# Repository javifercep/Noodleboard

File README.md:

# Noodleboard
Arduino form factor board with USB 2.0 High speed based on STM32F405 MCU.
It has been developed for the [MuBA project](https://gitlab.euridies.com/javi/MuBA)

## Features
 * STM32F405RGT6 microcontroller featuring 32-bit ARM Cortex-M4F core, 1 MB Flash, 192 KB RAM in an LQFP64 package
 * Extension header fully compatible with Arduino™ form-factor
 * USB3300: USB OTG HS with micro-AB connector
 * Board power supply: through USB bus.
 * External application power supply: 3.3 V and 5 V
 * Four green user LEDs
 * Reset button
 * Headers for programming and debugging through SWD protocol

## [Pin map](pin-map)

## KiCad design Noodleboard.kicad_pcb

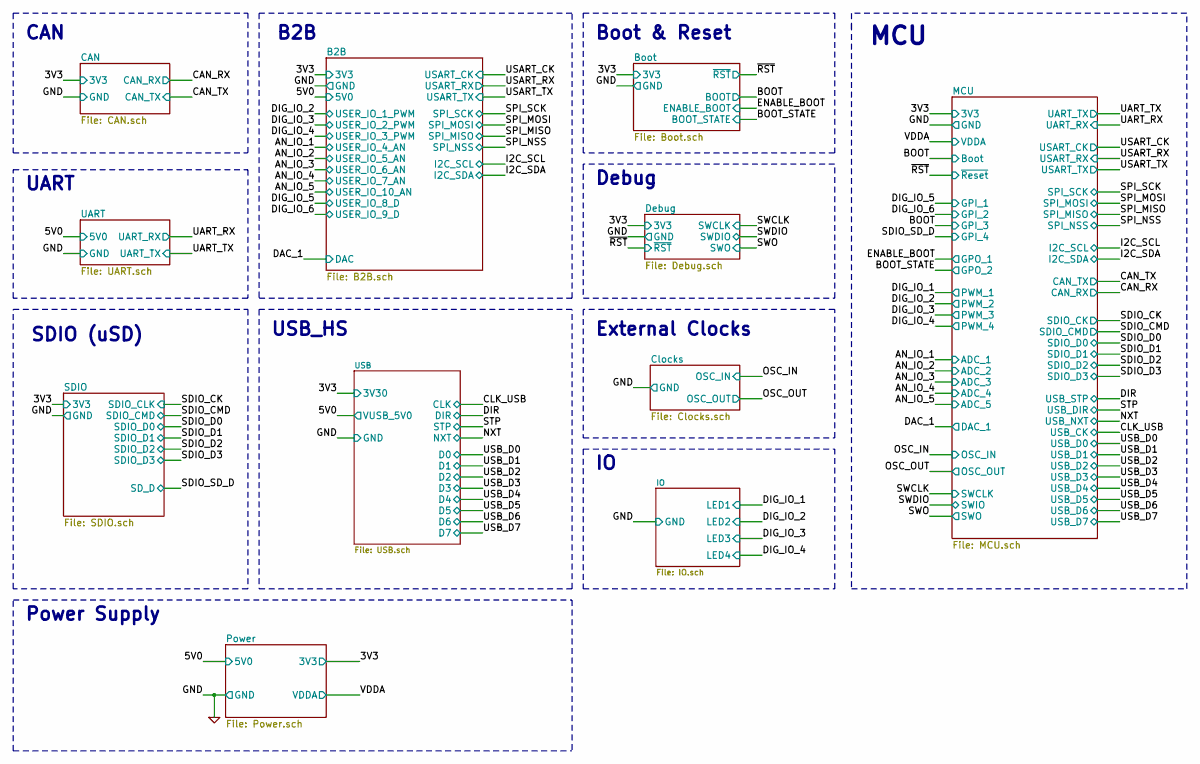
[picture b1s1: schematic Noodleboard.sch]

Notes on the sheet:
Power Supply
USB_HS
Debug
External Clocks
MCU
Boot & Reset
CAN
UART
B2B
SDIO (uSD)

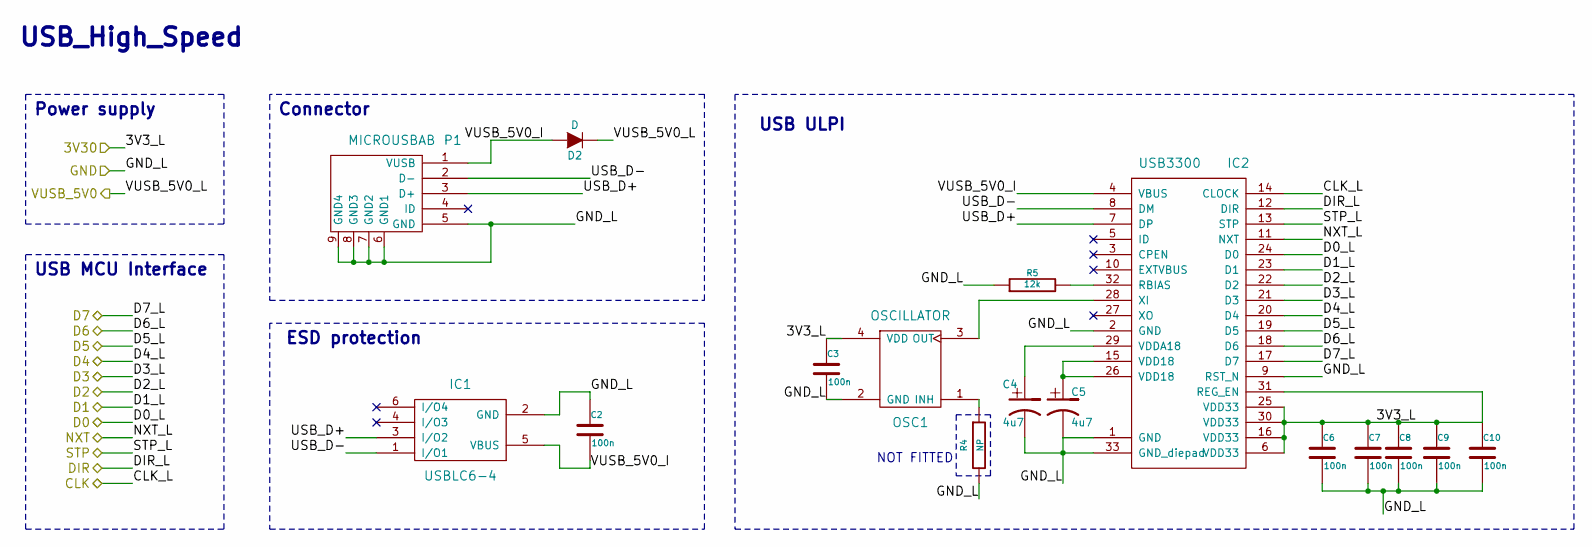
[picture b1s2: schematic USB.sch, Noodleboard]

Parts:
C2, C3, C6, C7, C8, C9, C10: 100n; C_0603_HandSoldering
C4, C5: 4u7; C_0805_HandSoldering
D2: D; SMA_Handsoldering
IC1: USBLC6-4; SOT-23-6
IC2: USB3300; QFN-32-1EP_5x5mm_Pitch0.5mm
OSC1: OSCILLATOR; 26MHZOSC
P1: MICROUSBAB; uUSB-AB
R4: NP; R_0603_HandSoldering
R5: 12k; R_0603_HandSoldering; Tolerancia 1%

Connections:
/B2B/3V3: C3.1, C6.1, C7.1, C8.1, C9.1, C10.1, IC2.6 (VDD33), IC2.16 (VDD33), IC2.25 (VDD33), IC2.30 (VDD33), IC2.31 (REG_EN), OSC1.4 (VDD); also elsewhere on the board
/B2B/5V0: D2.1 (K); also elsewhere on the board
/USB/CLK: IC2.14 (CLOCK); also elsewhere on the board
/USB/D0: IC2.24 (D0); also elsewhere on the board
/USB/D1: IC2.23 (D1); also elsewhere on the board
/USB/D2: IC2.22 (D2); also elsewhere on the board
/USB/D3: IC2.21 (D3); also elsewhere on the board
/USB/D4: IC2.20 (D4); also elsewhere on the board
/USB/D5: IC2.19 (D5); also elsewhere on the board
/USB/D6: IC2.18 (D6); also elsewhere on the board
/USB/D7: IC2.17 (D7); also elsewhere on the board
/USB/DIR: IC2.12 (DIR); also elsewhere on the board
/USB/NXT: IC2.11 (NXT); also elsewhere on the board
/USB/STP: IC2.13 (STP); also elsewhere on the board
/USB/USB_D+: IC1.3 (I/O2), IC2.7 (DP), P1.3 (D+)
/USB/USB_D-: IC1.1 (I/O1), IC2.8 (DM), P1.2 (D-)
/USB/VUSB_5V0_I: C2.2, D2.2 (A), IC1.5 (VBUS), IC2.4 (VBUS), P1.1 (VUSB)
GND: C2.1, C3.2, C4.2, C5.2, C6.2, C7.2, C8.2, C9.2, C10.2, IC1.2 (GND), IC2.1 (GND), IC2.2 (GND), IC2.9 (RST_N), IC2.33 (GND_diepad), OSC1.2 (GND), P1.5 (GND), P1.6 (GND1), P1.7 (GND2), P1.8 (GND3), P1.9 (GND4), R4.2, R5.1; also elsewhere on the board
unnamed: C4.1, IC2.29 (VDDA18)
unnamed: C5.1, IC2.15 (VDD18), IC2.26 (VDD18)
unnamed: IC2.28 (XI), OSC1.3 (OUT)
unnamed: IC2.32 (RBIAS), R5.2
unnamed: OSC1.1 (INH), R4.1

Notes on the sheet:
Power supply
USB_High_Speed
NOT FITTED
Connector
ESD protection
USB MCU Interface
USB ULPI

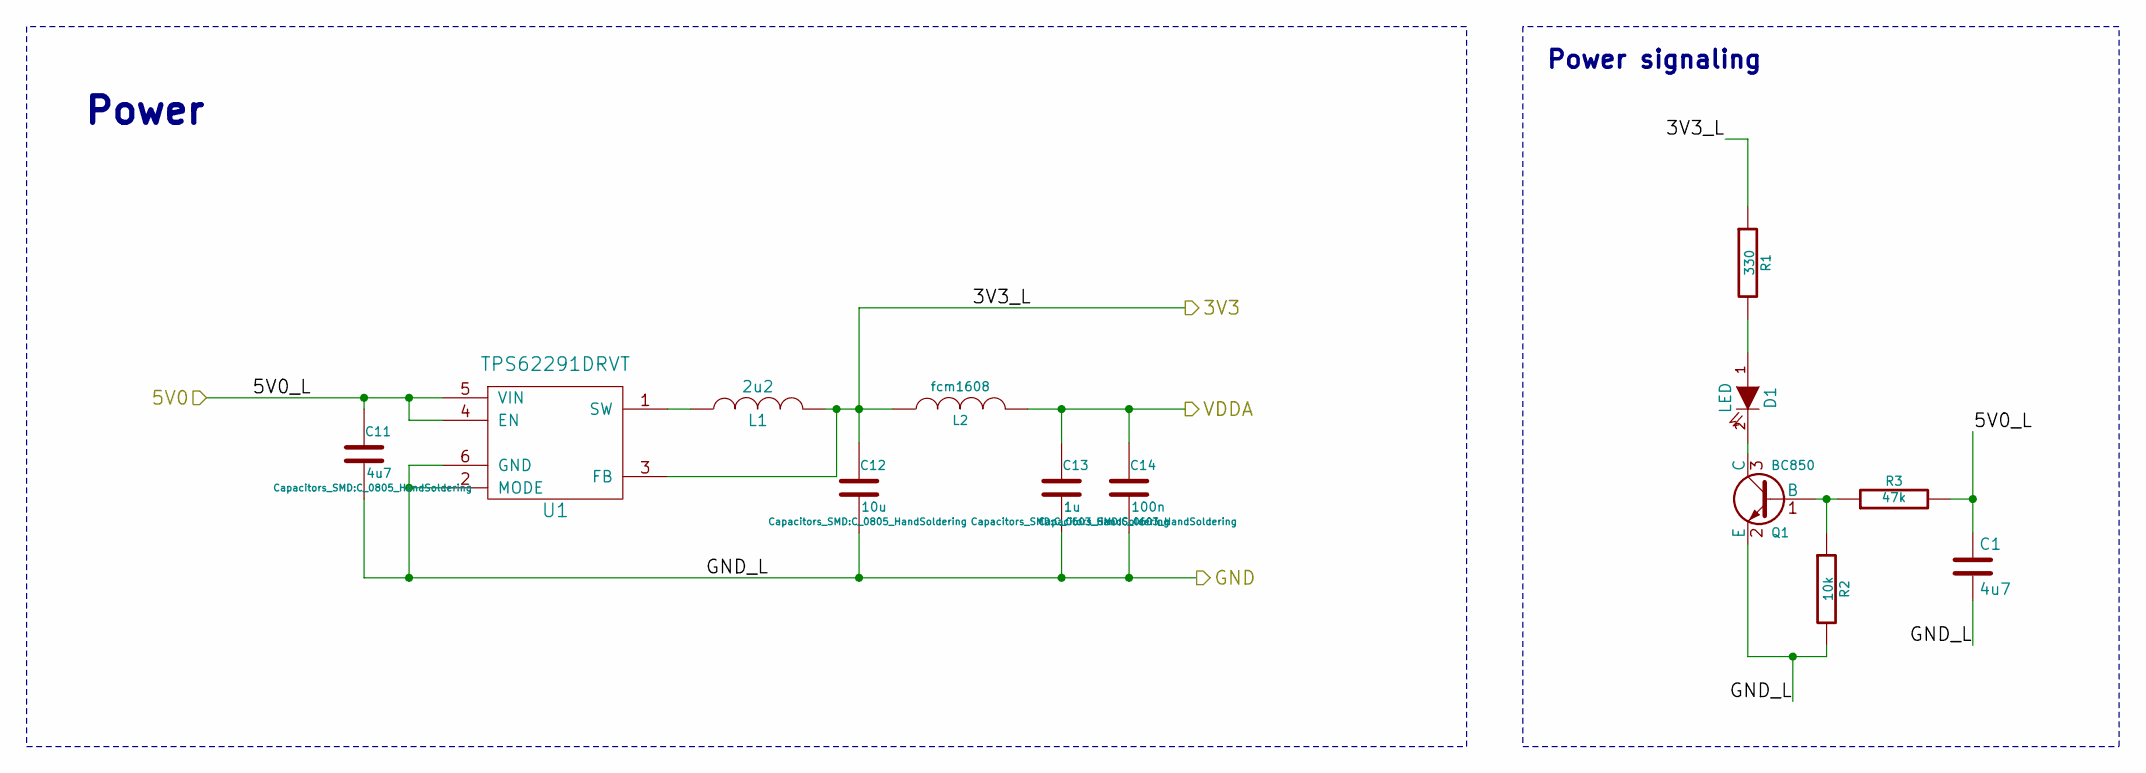
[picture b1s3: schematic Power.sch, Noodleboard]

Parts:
C1: 4u7; C_0805_HandSoldering
C11: 4u7; C_0805_HandSoldering; Part Number GRM188R60J475KE19D
C12: 10u; C_0805_HandSoldering; Part Number C1608X5R0J106M
C13: 1u; C_0603_HandSoldering
C14: 100n; C_0603_HandSoldering
D1: LED; LED-0805
L1: 2u2; SMD_1008; Part Number 74479887222A
L2: fcm1608; R_0603_HandSoldering
Q1: BC850; SOT-23_Handsoldering
R1: 330; R_0603_HandSoldering
R2: 10k; R_0603_HandSoldering
R3: 47k; R_0603_HandSoldering
U1: TPS62291DRVT; S-PWSON-N6

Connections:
/B2B/3V3: C12.1, L1.2, L2.1, R1.1, U1.3 (FB); also elsewhere on the board
/B2B/5V0: C1.1, C11.1, R3.2, U1.4 (EN), U1.5 (VIN); also elsewhere on the board
/MCU/VDDA: C13.1, C14.1, L2.2; also elsewhere on the board
GND: C1.2, C11.2, C12.2, C13.2, C14.2, Q1.2 (E), R2.2, U1.2 (MODE), U1.6 (GND); also elsewhere on the board
unnamed: D1.1 (A), R1.2
unnamed: D1.2 (K), Q1.3 (C)
unnamed: L1.1, U1.1 (SW)
unnamed: Q1.1 (B), R2.1, R3.1

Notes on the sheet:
Power
Power signaling

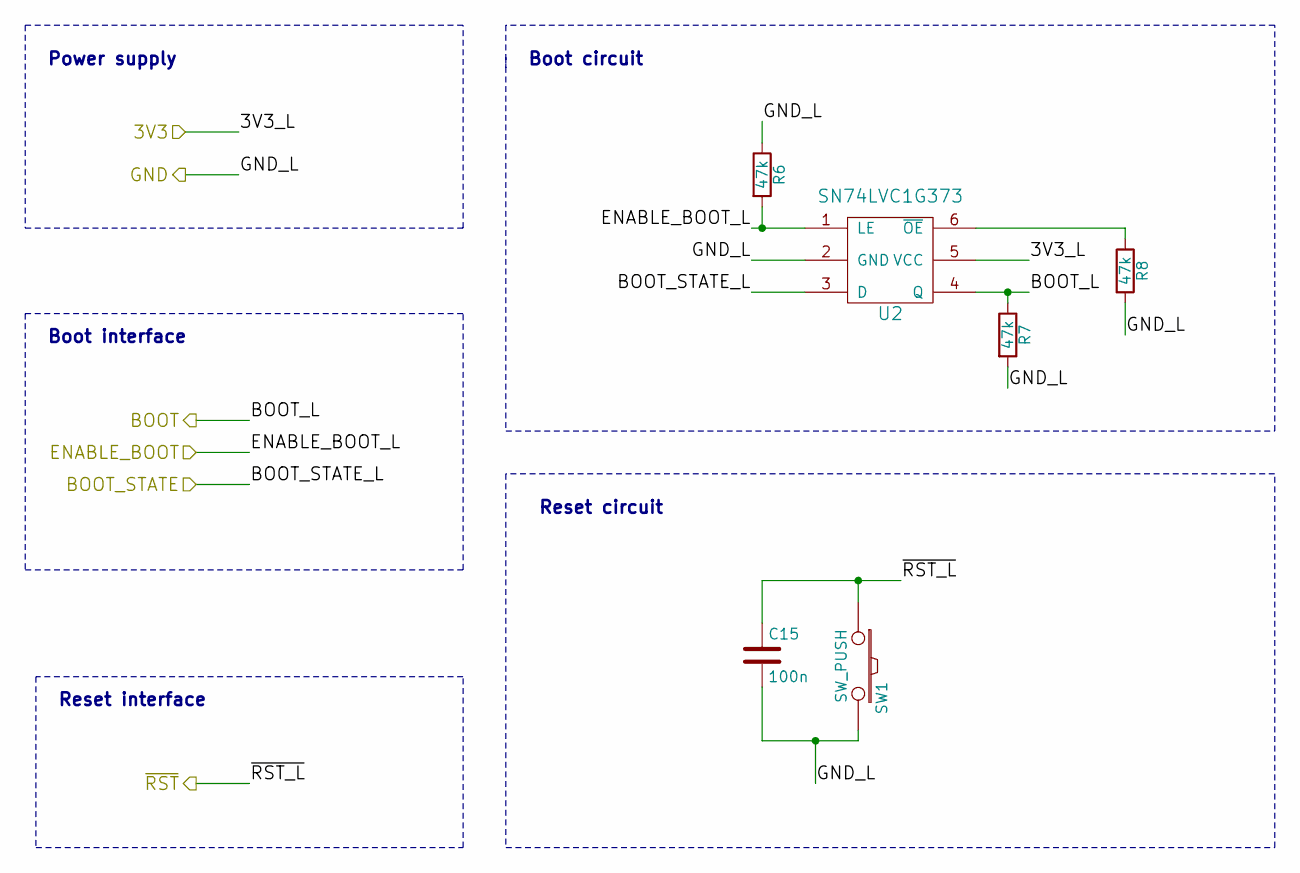
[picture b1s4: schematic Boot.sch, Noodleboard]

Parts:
C15: 100n; C_0603_HandSoldering
R6, R7, R8: 47k; R_0603_HandSoldering
SW1: SW_PUSH; SW_PUSH_SMALL_SMD
U2: SN74LVC1G373; SOT-23-6

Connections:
/B2B/3V3: U2.5 (VCC); also elsewhere on the board
/Boot/BOOT: R7.1, U2.4 (Q); also elsewhere on the board
/Boot/BOOT_STATE: U2.3 (D); also elsewhere on the board
/Boot/ENABLE_BOOT: R6.2, U2.1 (LE); also elsewhere on the board
/Boot/~RST: C15.1, SW1.1; also elsewhere on the board
GND: C15.2, R6.1, R7.2, R8.2, SW1.2, U2.2 (GND); also elsewhere on the board
unnamed: R8.1, U2.6 (~OE)

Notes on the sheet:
Reset circuit
Boot circuit
Power supply
Boot interface
Reset interface

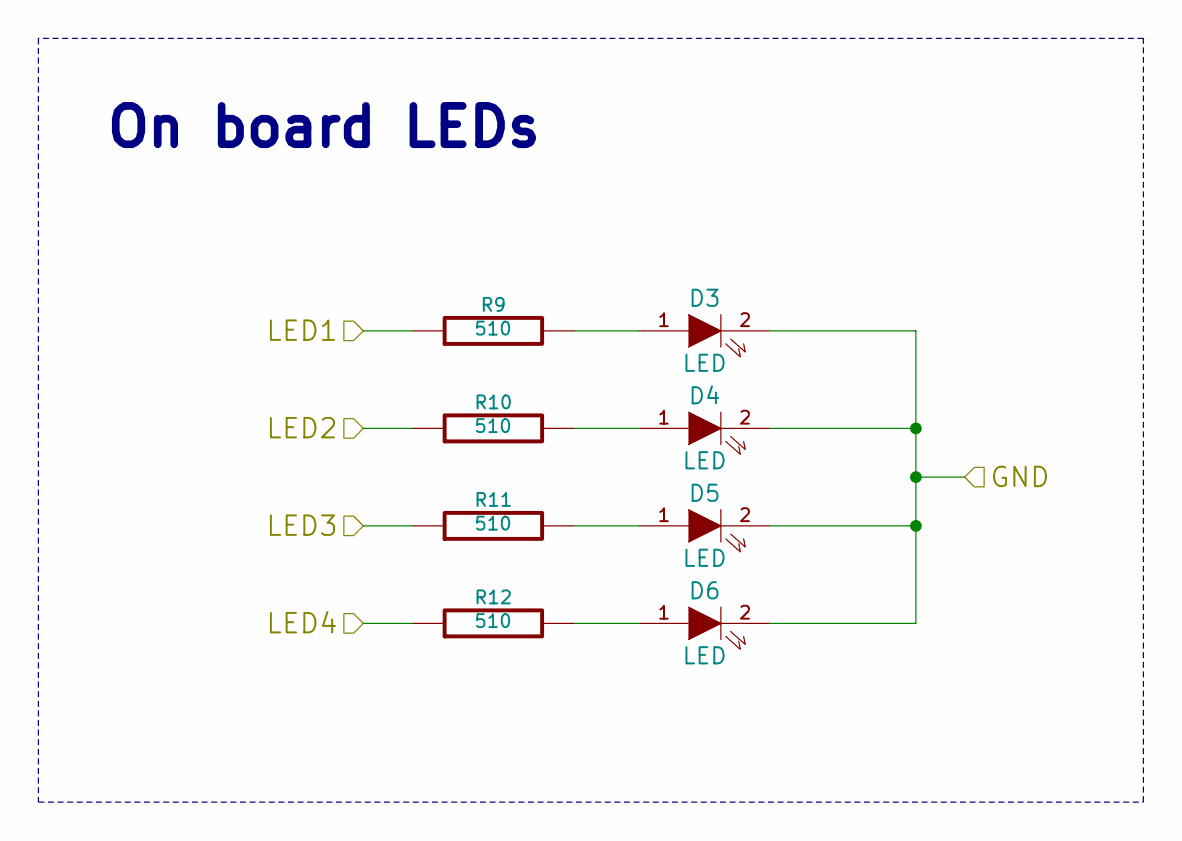
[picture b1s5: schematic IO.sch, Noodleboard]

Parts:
D3, D4, D5, D6: LED; LED-0805
R9, R10, R11, R12: 510; R_0603_HandSoldering

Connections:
/IO/LED1: R9.1; also elsewhere on the board
/IO/LED2: R10.1; also elsewhere on the board
/IO/LED3: R11.1; also elsewhere on the board
/IO/LED4: R12.1; also elsewhere on the board
GND: D3.2 (K), D4.2 (K), D5.2 (K), D6.2 (K); also elsewhere on the board
unnamed: D3.1 (A), R9.2
unnamed: D4.1 (A), R10.2
unnamed: D5.1 (A), R11.2
unnamed: D6.1 (A), R12.2

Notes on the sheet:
On board LEDs

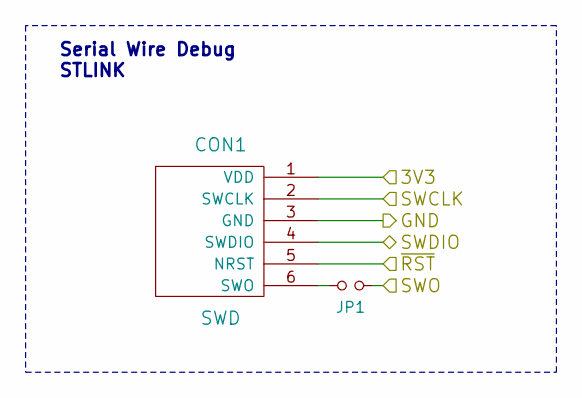
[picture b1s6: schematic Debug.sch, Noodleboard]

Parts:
CON1: SWD; Pin_Header_Straight_1x06
JP1: Jumper_NO_Small; R_0603_HandSoldering

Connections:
/B2B/3V3: CON1.1 (VDD); also elsewhere on the board
/B2B/SPI_SCK: JP1.2; also elsewhere on the board
/Boot/~RST: CON1.5 (NRST); also elsewhere on the board
/Debug/SWCLK: CON1.2 (SWCLK); also elsewhere on the board
/Debug/SWDIO: CON1.4 (SWDIO); also elsewhere on the board
GND: CON1.3 (GND); also elsewhere on the board
unnamed: CON1.6 (SWO), JP1.1

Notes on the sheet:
Serial Wire Debug STLINK

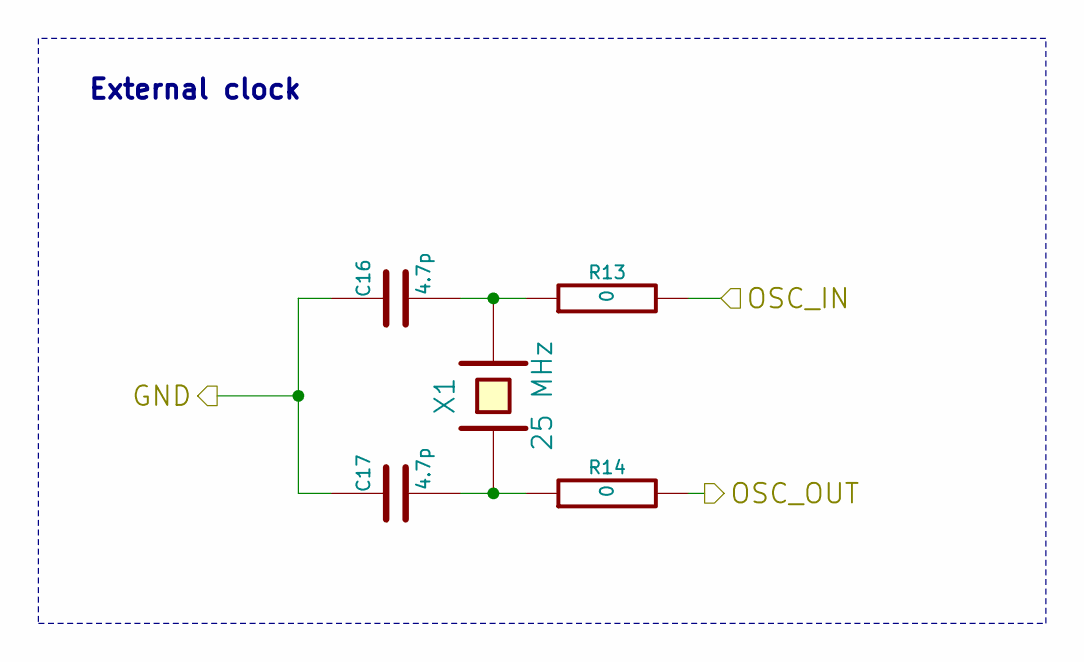
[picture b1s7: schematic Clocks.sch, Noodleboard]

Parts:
C16, C17: 4.7p; C_0603_HandSoldering
R13, R14: 0; R_0603_HandSoldering
X1: 25 MHz; 7A-25.000MAAJ-T

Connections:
/Clocks/OSC_IN: R13.2; also elsewhere on the board
/Clocks/OSC_OUT: R14.2; also elsewhere on the board
GND: C16.1, C17.1; also elsewhere on the board
unnamed: C16.2, R13.1, X1.2
unnamed: C17.2, R14.1, X1.1

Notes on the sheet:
External clock

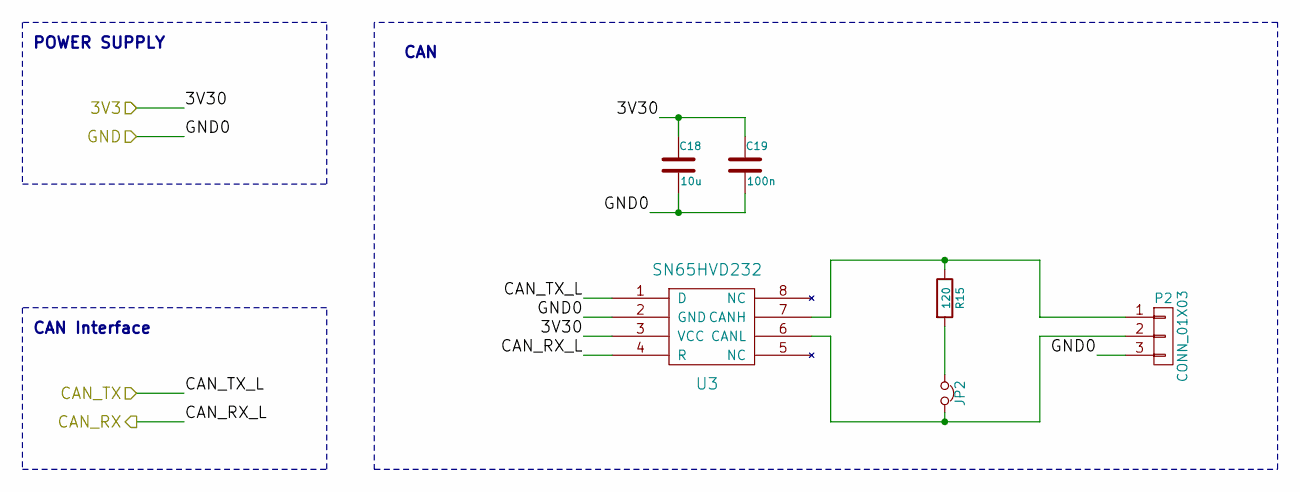
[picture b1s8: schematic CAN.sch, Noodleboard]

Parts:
C18: 10u; C_0805_HandSoldering
C19: 100n; C_0603_HandSoldering
JP2: Jumper_NC_Small; AYZ-SlideSwitches
P2: CONN_01X03; Pin_Header_Straight_1x03
R15: 120; R_0805_HandSoldering
U3: SN65HVD232; SOIC-8_3.9x4.9mm_Pitch1.27mm

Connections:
/B2B/3V3: C18.1, C19.1, U3.3 (VCC); also elsewhere on the board
/CAN/CAN_RX: U3.4 (R); also elsewhere on the board
/CAN/CAN_TX: U3.1 (D); also elsewhere on the board
GND: C18.2, C19.2, P2.3, U3.2 (GND); also elsewhere on the board
unnamed: JP2.1, R15.2
unnamed: JP2.2, P2.2, U3.6 (CANL)
unnamed: P2.1, R15.1, U3.7 (CANH)

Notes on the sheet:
POWER SUPPLY
CAN
CAN Interface

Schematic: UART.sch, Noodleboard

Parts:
C20, C21, C22, C23, C24: 1u; C_0603_HandSoldering
P3: CONN_01X03; Pin_Header_Straight_1x03
U4: MAX232; SOIC-16_3.9x9.9mm_Pitch1.27mm

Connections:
/B2B/5V0: C24.1, U4.16 (VCC); also elsewhere on the board
/MCU/UART_RX: U4.12 (R1OUT); also elsewhere on the board
/MCU/UART_TX: U4.11 (T1IN); also elsewhere on the board
GND: C22.1, C23.1, C24.2, P3.1, U4.15 (GND); also elsewhere on the board
unnamed: C20.1, U4.1 (C1+)
unnamed: C20.2, U4.3 (C1-)
unnamed: C21.1, U4.4 (C2+)
unnamed: C21.2, U4.5 (C2-)
unnamed: C22.2, U4.2 (V+)
unnamed: C23.2, U4.6 (V-)
unnamed: P3.2, U4.14 (T1OUT)
unnamed: P3.3, U4.13 (R1IN)

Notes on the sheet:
POWER SUPPLY
UART

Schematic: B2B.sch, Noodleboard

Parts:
P4: CONN_01X14; Pin_Header_Straight_1x14
P5: CONN_02X07; Pin_Header_Straight_2x07

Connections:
/B2B/3V3: P4.1, P5.1; also elsewhere on the board
/B2B/5V0: P4.13, P5.12; also elsewhere on the board
/B2B/DAC: P4.14; also elsewhere on the board
/B2B/I2C_SCL: P4.11; also elsewhere on the board
/B2B/I2C_SDA: P4.12; also elsewhere on the board
/B2B/SPI_MISO: P4.8; also elsewhere on the board
/B2B/SPI_MOSI: P4.7; also elsewhere on the board
/B2B/SPI_NSS: P4.9; also elsewhere on the board
/B2B/SPI_SCK: P4.6; also elsewhere on the board
/B2B/USART_CK: P4.2; also elsewhere on the board
/B2B/USART_RX: P4.3; also elsewhere on the board
/B2B/USART_TX: P4.4; also elsewhere on the board
/IO/LED2: P5.3; also elsewhere on the board
/IO/LED3: P5.5; also elsewhere on the board
/IO/LED4: P5.7; also elsewhere on the board
/MCU/ADC_1: P5.11; also elsewhere on the board
/MCU/ADC_2: P5.13; also elsewhere on the board
/MCU/ADC_3: P5.2; also elsewhere on the board
/MCU/ADC_4: P5.4; also elsewhere on the board
/MCU/ADC_5: P5.14; also elsewhere on the board
/MCU/GPI_1: P5.8; also elsewhere on the board
/MCU/GPI_2: P5.10; also elsewhere on the board
GND: P4.5, P4.10, P5.6, P5.9; also elsewhere on the board

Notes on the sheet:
Board to board connector

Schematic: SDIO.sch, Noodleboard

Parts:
R16, R17, R18, R19, R20: 47K; R_0603_HandSoldering
R21: 0; R_0603_HandSoldering
U5: SD_CARD; uSDCard

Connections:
/B2B/3V3: R16.2, R17.2, R18.2, R19.2, R20.2, U5.4 (VDD); also elsewhere on the board
/MCU/GPI_4: R21.2; also elsewhere on the board
/MCU/SDIO_CK: U5.5 (CLK); also elsewhere on the board
/MCU/SDIO_CMD: R16.1, U5.3 (CMD); also elsewhere on the board
/MCU/SDIO_D0: R17.1, U5.7 (DAT0); also elsewhere on the board
/MCU/SDIO_D1: R18.1, U5.8 (DAT1); also elsewhere on the board
/MCU/SDIO_D2: R19.1, U5.1 (DAT2); also elsewhere on the board
/MCU/SDIO_D3: R20.1, U5.2 (CD/DAT3); also elsewhere on the board
/SDIO/CD: R21.1, U5.10 (CD)
GND: U5.6 (VSS), U5.9 (DL(GND)); also elsewhere on the board

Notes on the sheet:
SD Card Connector
Power supply
SDIO interface
SD Card detection

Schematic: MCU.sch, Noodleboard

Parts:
C25, C26: 2u2; C_0805_HandSoldering
C27, C28, C29, C30, C32: 100n; C_0603_HandSoldering
C31: 1u; C_0603_HandSoldering
C33: 4u7; C_0805_HandSoldering
JP3, JP4: Jumper_NO_Small; R_0603_HandSoldering
R22: 0; R_0603_HandSoldering
R23: 1K; R_0603_HandSoldering
R24: 47; R_0603_HandSoldering
U6: STM32F405RGT6; LQFP-64_10x10mm_Pitch0.5mm

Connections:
/B2B/3V3: C27.2, C28.1, C29.2, C30.2, C32.2, C33.1, R24.1, U6.19 (VDD), U6.32 (VDD), U6.48 (VDD), U6.64 (VDD); also elsewhere on the board
/B2B/DAC: U6.20 (PA4); also elsewhere on the board
/B2B/I2C_SCL: U6.61 (PB8); also elsewhere on the board
/B2B/I2C_SDA: U6.62 (PB9); also elsewhere on the board
/B2B/SPI_MISO: U6.56 (PB4); also elsewhere on the board
/B2B/SPI_MOSI: U6.23 (PA7); also elsewhere on the board
/B2B/SPI_NSS: U6.50 (PA15); also elsewhere on the board
/B2B/SPI_SCK: U6.55 (PB3); also elsewhere on the board
/B2B/USART_CK: U6.41 (PA8); also elsewhere on the board
/B2B/USART_RX: U6.43 (PA10); also elsewhere on the board
/B2B/USART_TX: U6.42 (PA9); also elsewhere on the board
/Boot/BOOT: R22.2, U6.4 (PC15); also elsewhere on the board
/Boot/BOOT_STATE: U6.35 (PB14); also elsewhere on the board
/Boot/ENABLE_BOOT: U6.36 (PB15); also elsewhere on the board
/Boot/~RST: U6.7 (NRST); also elsewhere on the board
/CAN/CAN_RX: U6.44 (PA11); also elsewhere on the board
/CAN/CAN_TX: U6.45 (PA12); also elsewhere on the board
/Clocks/OSC_IN: U6.5 (PH0); also elsewhere on the board
/Clocks/OSC_OUT: U6.6 (PH1); also elsewhere on the board
/Debug/SWCLK: U6.49 (PA14); also elsewhere on the board
/Debug/SWDIO: U6.46 (PA13); also elsewhere on the board
/IO/LED1: U6.38 (PC7); also elsewhere on the board
/IO/LED2: U6.37 (PC6); also elsewhere on the board
/IO/LED3: U6.59 (PB7); also elsewhere on the board
/IO/LED4: U6.58 (PB6); also elsewhere on the board
/MCU/ADC_1: U6.9 (PC1); also elsewhere on the board
/MCU/ADC_2: U6.16 (PA2); also elsewhere on the board
/MCU/ADC_3: U6.22 (PA6); also elsewhere on the board
/MCU/ADC_4: U6.24 (PC4); also elsewhere on the board
/MCU/ADC_5: U6.25 (PC5); also elsewhere on the board
/MCU/BOOT_L: R22.1, R23.2, U6.60 (BOOT0)
/MCU/GPI_1: U6.2 (PC13); also elsewhere on the board
/MCU/GPI_2: U6.3 (PC14); also elsewhere on the board
/MCU/GPI_4: U6.28 (PB2); also elsewhere on the board
/MCU/SDIO_CK: U6.53 (PC12); also elsewhere on the board
/MCU/SDIO_CMD: U6.54 (PD2); also elsewhere on the board
/MCU/SDIO_D0: U6.39 (PC8); also elsewhere on the board
/MCU/SDIO_D1: U6.40 (PC9); also elsewhere on the board
/MCU/SDIO_D2: U6.51 (PC10); also elsewhere on the board
/MCU/SDIO_D3: U6.52 (PC11); also elsewhere on the board
/MCU/UART_RX: U6.15 (PA1); also elsewhere on the board
/MCU/UART_TX: U6.14 (PA0_WKUP); also elsewhere on the board
/MCU/VBAT_L: C31.1, R24.2, U6.1 (VBAT)
/MCU/VCAP_1: C25.1, JP4.1, U6.31 (VCAP_1)
/MCU/VCAP_2: C26.1, JP3.1, U6.47 (VCAP_2)
/MCU/VDDA: U6.13 (VDDA); also elsewhere on the board
/USB/CLK: U6.21 (PA5); also elsewhere on the board
/USB/D0: U6.17 (PA3); also elsewhere on the board
/USB/D1: U6.26 (PB0); also elsewhere on the board
/USB/D2: U6.27 (PB1); also elsewhere on the board
/USB/D3: U6.29 (PB10); also elsewhere on the board
/USB/D4: U6.30 (PB11); also elsewhere on the board
/USB/D5: U6.33 (PB12); also elsewhere on the board
/USB/D6: U6.34 (PB13); also elsewhere on the board
/USB/D7: U6.57 (PB5); also elsewhere on the board
/USB/DIR: U6.8 (PC0); also elsewhere on the board
/USB/NXT: U6.11 (PC3); also elsewhere on the board
/USB/STP: U6.10 (PC2); also elsewhere on the board
GND: C25.2, C26.2, C27.1, C28.2, C29.1, C30.1, C31.2, C32.1, C33.2, JP3.2, JP4.2, R23.1, U6.12 (VSSA), U6.18 (VSS), U6.63 (VSS); also elsewhere on the board

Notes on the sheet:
MCU: STM32F405RG / STM32F105
0 resistor - Mount: STM32F105, - Unmount: STM32F405
Power inputs
Decoupling capacitors
Reset & boot
External Clock
USB_HS
Debug
UART & USART
SPI
CAN
I2C
SDIO
MCU MAPPING
Power scheme adaptor STM32F105/STM32F405
VBAT stabilization

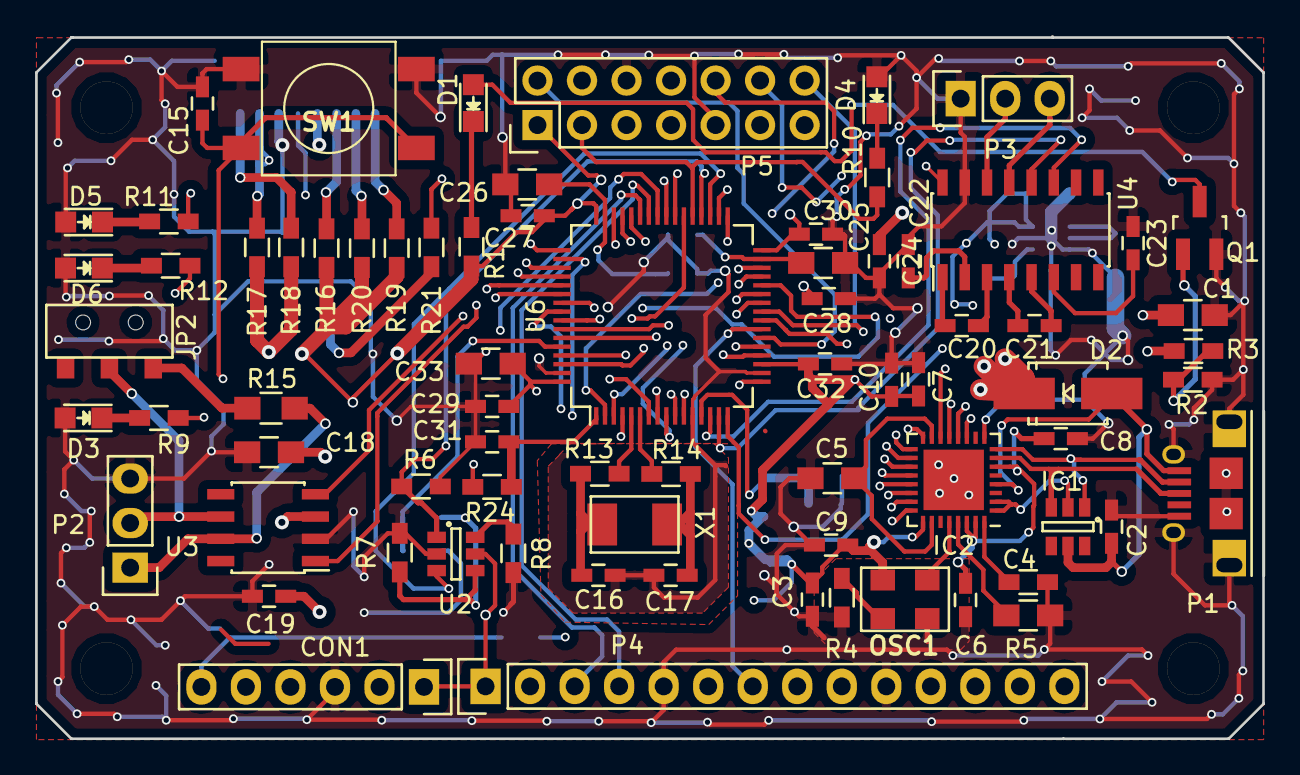
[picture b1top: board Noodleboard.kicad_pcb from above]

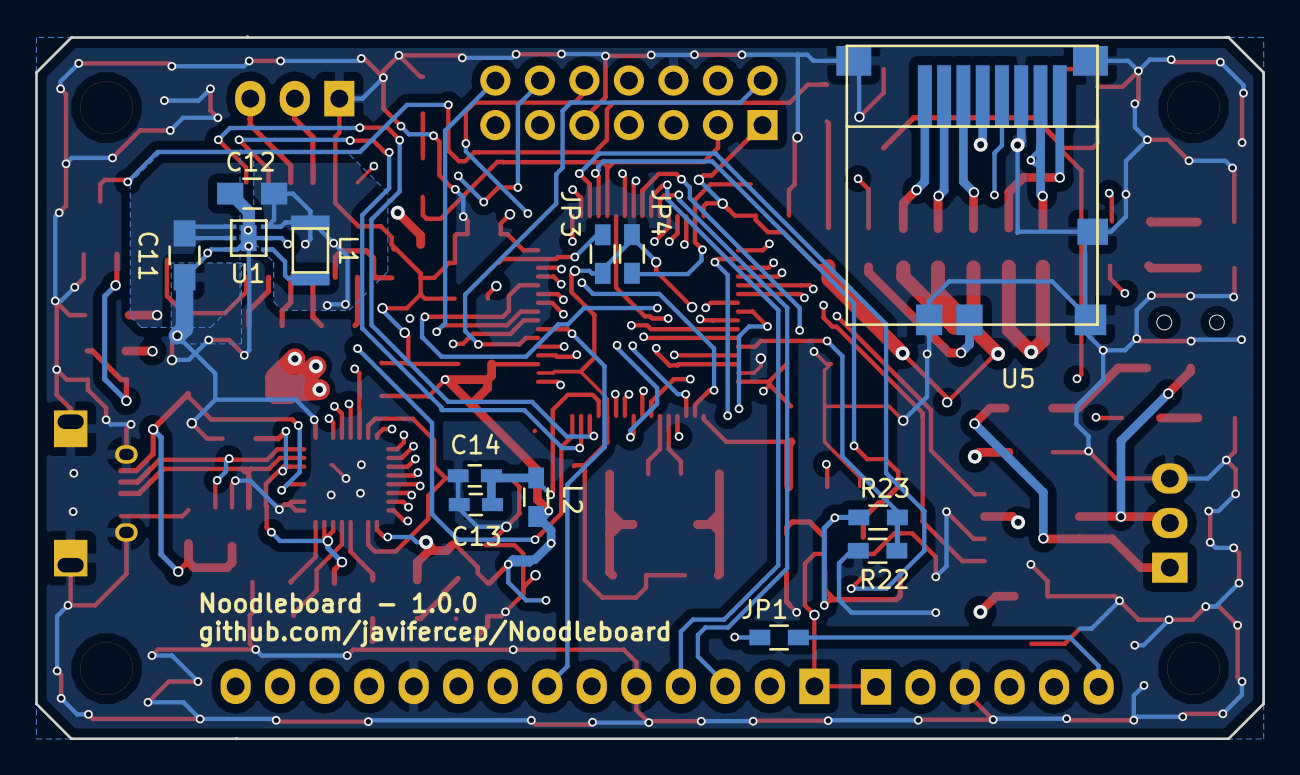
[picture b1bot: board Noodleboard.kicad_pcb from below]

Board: 4 copper layers, 70.0 x 40.0 mm, 91 parts (13 on the bottom side), 92 nets.

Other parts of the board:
Hole3mm, Hole3mm#2, Hole3mm#3, Hole3mm#4: VAL**; Hole3mm

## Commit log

2015-05-23 Added License and gitignore file
2015-05-23 Added initial design
2015-10-03 Updated .gitignore file
2015-10-03 #3 Add SD card interface #4 Add CAN & UART transceivers
2015-11-07 - #4 Added UART and CAN interface transceivers - Improved schematic structure - Removed all gerber outputs - Generated schematics outputs for PCB design - Updated local libraries
2015-11-07 - New PCB design - Updated last schematics modifications - Added Gerber outputs (old and new version)
2015-11-07 Updated documentation (Sch & PCB)
2015-11-08 #5 Review USB power supply #6 Power signaling LED should be in power sheet - Simplified outputs (Gerber, sch & pcb)
